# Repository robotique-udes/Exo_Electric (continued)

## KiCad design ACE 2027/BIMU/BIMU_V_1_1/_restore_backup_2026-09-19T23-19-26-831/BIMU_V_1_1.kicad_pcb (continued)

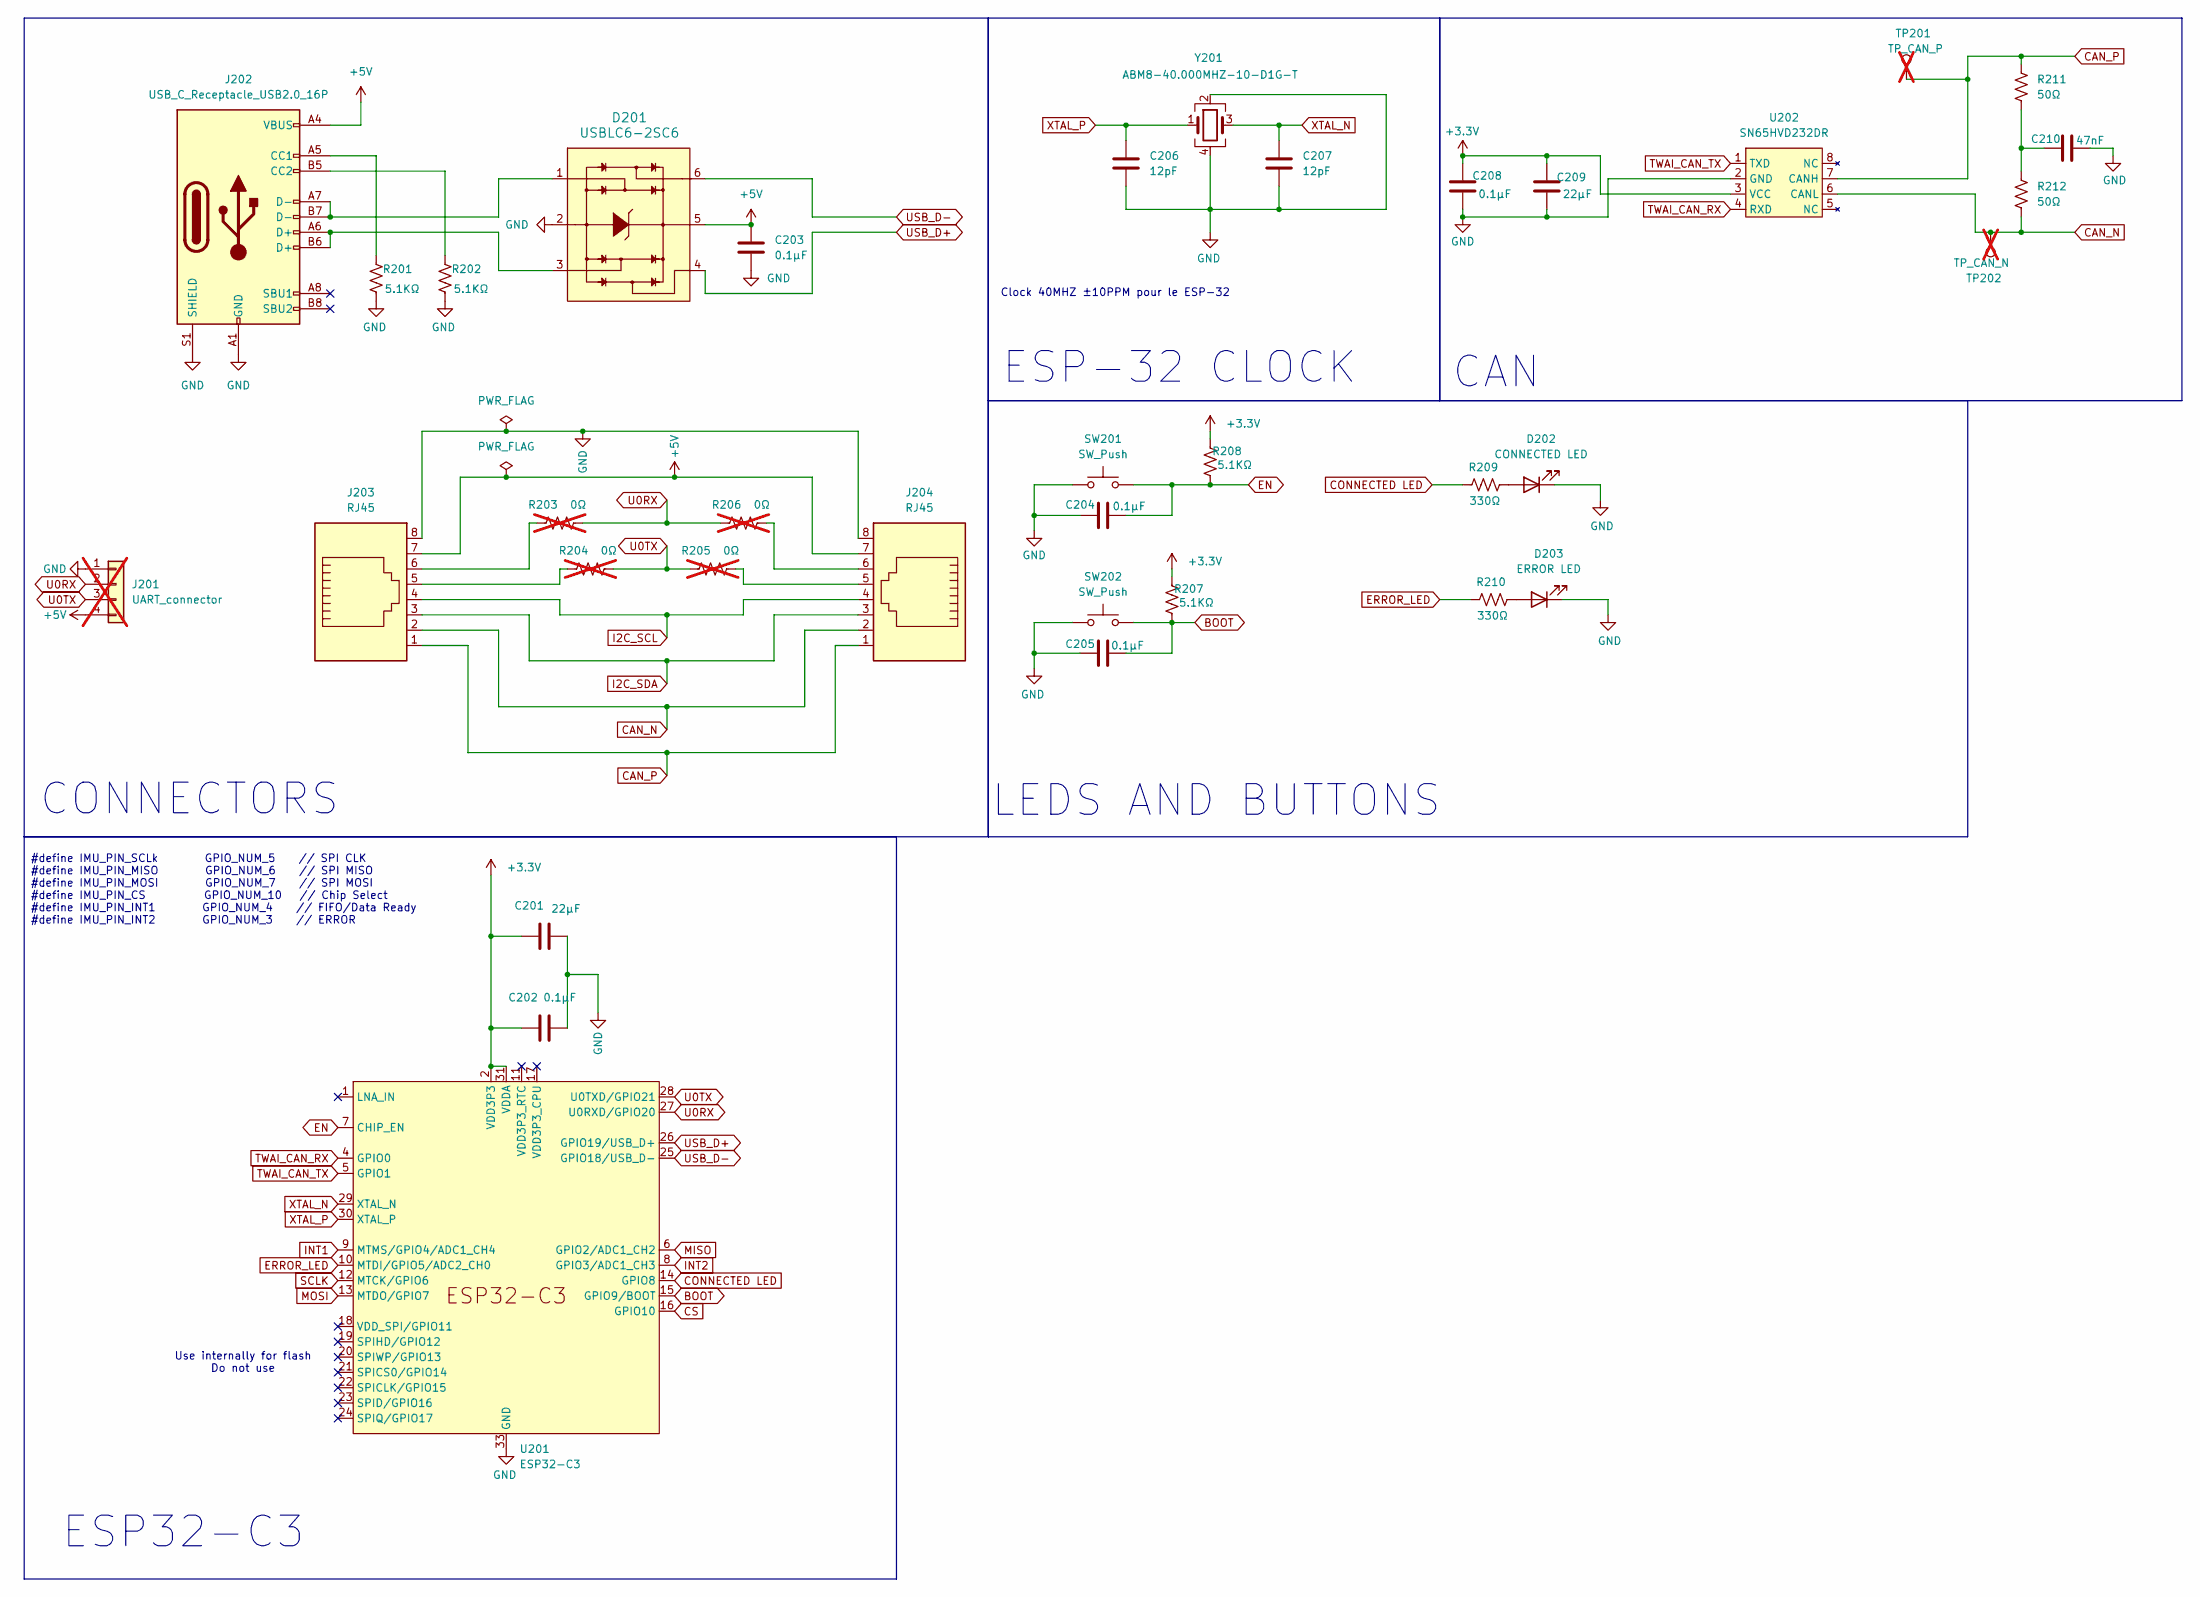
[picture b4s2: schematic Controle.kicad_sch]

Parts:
C201, C209: 22μF; C_0805_2012Metric_Pad1.18x1.45mm_HandSolder; Digi-Key_PN 1276-6501-1-ND
C202, C203, C204, C205, C208: 0.1μF; C_0805_2012Metric_Pad1.18x1.45mm_HandSolder; Digi-Key_PN 399-C0805C104K5RACTUCT-ND
C206, C207: 12pF; C_0805_2012Metric_Pad1.18x1.45mm_HandSolder; Digi-Key_PN 399-C0805C120J8HACTUCT-ND
C210: 47nF; C_0603_1608Metric_Pad1.08x0.95mm_HandSolder; Digi-Key_PN 1276-2960-1-ND
D201: USBLC6-2SC6; SOT23-6L; MPN USBLC6-2SC6; Digi-Key_PN 4518-USBLC6-2SC6CT-ND
D202: CONNECTED LED; LED_0805_2012Metric_Pad1.15x1.40mm_HandSolder; Digi-Key_PN 1516-QBLP631-IB5CT-ND
D203: ERROR LED; LED_0805_2012Metric_Pad1.15x1.40mm_HandSolder; Digi-Key_PN 1516-QBLP631-R5-2897CT-ND
J201: UART_connector; PinSocket_1x04_P2.54mm_Vertical; not fitted
J202: USB_C_Receptacle_USB2.0_16P; USB_C_Receptacle_GCT_USB4105-xx-A_16P_TopMnt_Horizontal; Digi-Key_PN 2073-USB4105-GF-ACT-ND
J203, J204: RJ45; RJ45_Amphenol_54602-x08_Horizontal; Digi-Key_PN 609-1046-ND
R201, R202, R207, R208: 5.1KΩ; R_0805_2012Metric_Pad1.20x1.40mm_HandSolder; Digi-Key_PN 541-CRCW08055K10FKEACCT-ND
R203, R204, R205, R206: 0Ω; R_0402_1005Metric_Pad0.72x0.64mm_HandSolder; not fitted
R209, R210: 330Ω; R_0805_2012Metric_Pad1.20x1.40mm_HandSolder; Digi-Key_PN 541-4168-1-ND
R211, R212: 50Ω; R_0805_2012Metric_Pad1.20x1.40mm_HandSolder; Digi-Key_PN 541-CRCW080550R0FKTACT-ND
SW201, SW202: SW_Push; SW_SPST_B3U-1000P; Digi-Key_PN SW1021CT-ND
TP201: TP_CAN_P; TestPoint_Pad_1.0x1.0mm; not fitted
TP202: TP_CAN_N; TestPoint_Pad_1.0x1.0mm; not fitted
U201: ESP32-C3; QFN-32-1EP_5x5mm_P0.5mm_EP3.45x3.45mm; Digi-Key_PN 1904-ESP32-C3FH4CT-ND
U202: SN65HVD232DR; SOIC-8_3.9x4.9mm_P1.27mm; Digi-Key_PN 296-26344-1-ND
Y201: ABM8-40.000MHZ-10-D1G-T; Crystal_SMD_2016-4Pin_2.0x1.6mm; Digi-Key_PN 535-14997-1-ND

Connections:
+3.3V: C201.1, C202.1, C208.1, C209.1, R207.2, R208.2, U201.2 (VDD3P3), U201.3 (VDD3P3), U201.31 (VDDA), U201.32 (VDDA), U202.3 (VCC); also elsewhere on the board
+5V: C203.1, D201.5, J201.4, J202.A4 (VBUS), J202.A9 (VBUS), J202.B4 (VBUS), J202.B9 (VBUS), J203.7, J204.7; also elsewhere on the board
BOOT: C205.1, R207.1, SW202.2, U201.15 (GPIO9/BOOT)
CAN_N: J203.2, J204.2, R212.2, TP202.1 (1_1), U202.6 (CANL); also elsewhere on the board
CAN_P: J203.1, J204.1, R211.1, TP201.1 (1_1), U202.7 (CANH); also elsewhere on the board
CONNECTED LED: R209.2, U201.14 (GPIO8)
CS: U201.16 (GPIO10); also elsewhere on the board
EN: C204.1, R208.1, SW201.2, U201.7 (CHIP_EN)
ERROR_LED: R210.2, U201.10 (MTDI/GPIO5/ADC2_CH0)
GND: C201.2, C202.2, C203.2, C204.2, C205.2, C206.2, C207.2, C208.2, C209.2, C210.1, D201.2, D202.1 (K), D203.1 (K), J201.1, J202.A1 (GND), J202.A12 (GND), J202.B1 (GND), J202.B12 (GND), J202.S1 (SHIELD), J203.8, J204.8, R201.2, R202.2, SW201.1, SW202.1, U201.33 (GND), U202.2 (GND), Y201.2, Y201.4; also elsewhere on the board
I2C_SCL: J203.4, J204.4
I2C_SDA: J203.3, J204.3
INT1: U201.9 (MTMS/GPIO4/ADC1_CH4); also elsewhere on the board
INT2: U201.8 (GPIO3/ADC1_CH3); also elsewhere on the board
MISO: U201.6 (GPIO2/ADC1_CH2); also elsewhere on the board
MOSI: U201.13 (MTDO/GPIO7); also elsewhere on the board
unnamed: C210.2, R211.2, R212.1
unnamed: D201.1, J202.A7 (D-), J202.B7 (D-)
unnamed: D201.3, J202.A6 (D+), J202.B6 (D+)
unnamed: D202.2 (A), R209.1
unnamed: D203.2 (A), R210.1
unnamed: J202.A5 (CC1), R201.1
unnamed: J202.B5 (CC2), R202.1
unnamed: J203.5, R204.1
unnamed: J203.6, R203.1
unnamed: J204.5, R205.2
unnamed: J204.6, R206.2
SCLK: U201.12 (MTCK/GPIO6); also elsewhere on the board
TWAI_CAN_RX: U201.4 (GPIO0), U202.4 (RXD)
TWAI_CAN_TX: U201.5 (GPIO1), U202.1 (TXD)
U0RX: J201.2, R203.2, R206.1, U201.27 (U0RXD/GPIO20)
U0TX: J201.3, R204.2, R205.1, U201.28 (U0TXD/GPIO21)
USB_D+: D201.4, U201.26 (GPIO19/USB_D+)
USB_D-: D201.6, U201.25 (GPIO18/USB_D-)
XTAL_N: C207.1, U201.29 (XTAL_N), Y201.3
XTAL_P: C206.1, U201.30 (XTAL_P), Y201.1

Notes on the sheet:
ESP32-C3
#define IMU_PIN_SCLk GPIO_NUM_5 // SPI CLK #define IMU_PIN_MISO GPIO_NUM_6 // SPI MISO #define IMU_PIN_MOSI GPIO_NUM_7 // SPI MOSI #define IMU_PIN_CS GPIO_NUM_10 // Chip Select #define IMU_PIN_INT1 GPIO_NUM_4 // FIFO/Data Ready #define IMU_PIN_INT2 GPIO_NUM_3 // ERROR
CONNECTORS
Use internally for flash Do not use
ESP-32 CLOCK
LEDS AND BUTTONS
CAN
Clock 40MHZ ±10PPM pour le ESP-32

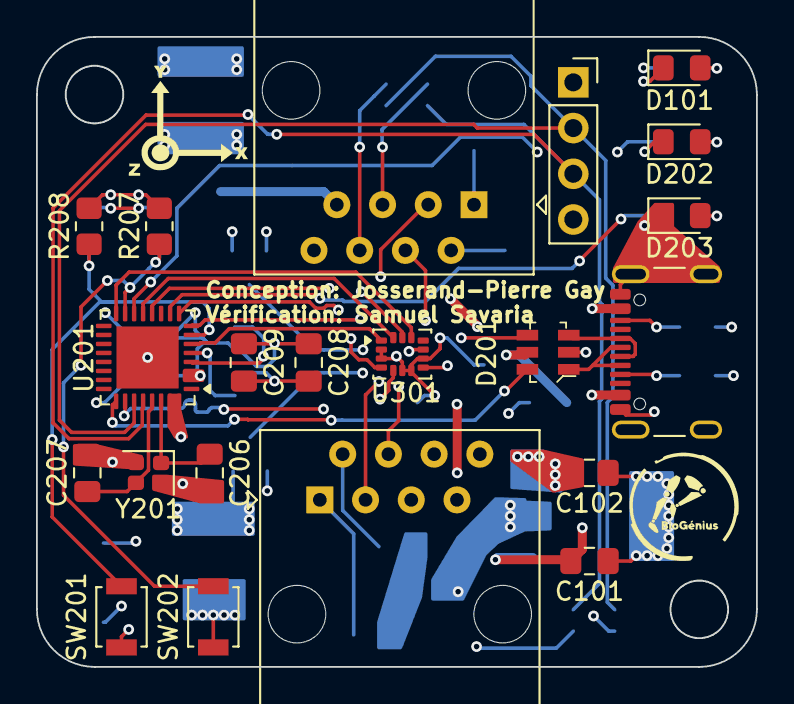
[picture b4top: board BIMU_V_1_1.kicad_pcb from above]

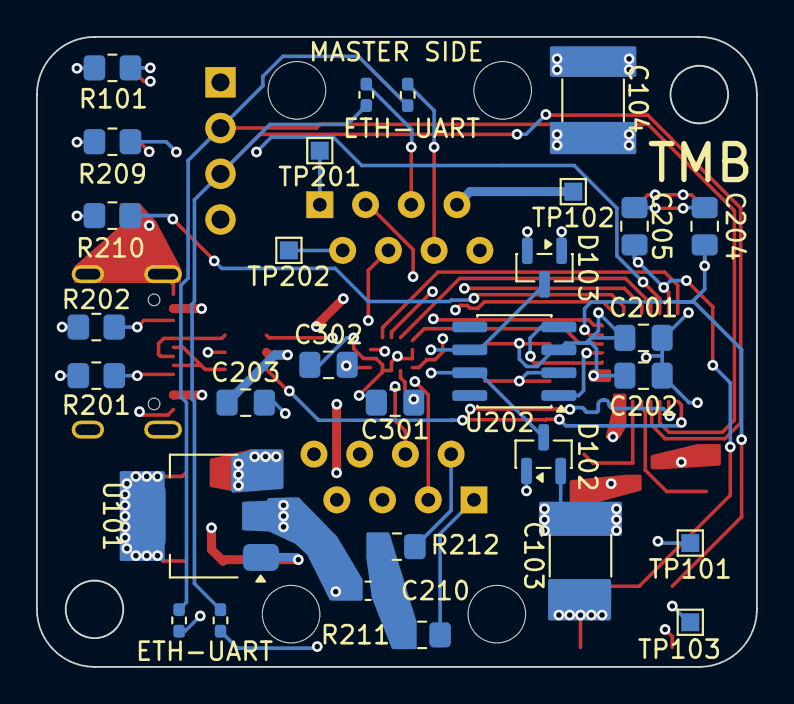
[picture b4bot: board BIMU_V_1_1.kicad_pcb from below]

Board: 4 copper layers, 40.0 x 35.0 mm, 53 parts (30 on the bottom side), 37 nets.

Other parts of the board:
C301, C302: 0.1μF; C_0805_2012Metric_Pad1.18x1.45mm_HandSolder
U301: LSM6DSV16BXTR; LGA-14_3x2.5mm_P0.5mm_LayoutBorder3x4y

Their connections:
+3.3V: C301.1, C302.2, U301.5 (VDDIO), U301.8 (VDD); also elsewhere on the board
CS: U301.12 (CS); also elsewhere on the board
GND: C301.2, C302.1, U301.2 (SDX), U301.3 (SCX), U301.6 (GND), U301.7 (GND), U301.9 (AH2); also elsewhere on the board
INT1: U301.4 (INT1); also elsewhere on the board
INT2: U301.10 (INT2); also elsewhere on the board
MISO: U301.1 (SDO/SA0); also elsewhere on the board
MOSI: U301.14 (SDA); also elsewhere on the board
SCLK: U301.13 (SCL); also elsewhere on the board

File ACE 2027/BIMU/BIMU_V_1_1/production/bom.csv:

Designator,Footprint,Quantity,Value,LCSC Part #
"C101, C102",0805,2,"4,7µF",
"C103, C104",1812,2,1nF,
"C201, C209",0805,2,22μF,
"C202, C203, C204, C205, C208, C301, C302",0805,7,0.1μF,
"C206, C207",0805,2,12pF,
C210,0603,1,47nF,
D101,0805,1,POWER LED,
"D102, D103",SOT-23,2,BAV99,
"D104, D105",0805,2,D_Schottky,
D201,SOT23-6L,1,USBLC6-2SC6,USBLC6-2SC6
D202,0805,1,CONNECTED LED,
D203,0805,1,ERROR LED,
J202,USB_C_Receptacle_GCT_USB4105-xx-A_16P_TopMnt_Horizontal,1,USB_C_Receptacle_USB2.0_16P,
"J203, J204",RJ45_Amphenol_54602-x08_Horizontal,2,RJ45,
"R101, R209, R210",0805,3,330Ω,
"R201, R202, R207, R208",0805,4,5.1KΩ,
"R203, R204, R205, R206",0402,4,0Ω,
"R211, R212",0805,2,50Ω,
"SW201, SW202",SW_SPST_B3U-1000P,2,SW_Push,
SW203,SW_SPDT_CK_JS102011SAQN,1,SW_CAN,
TP101,TestPoint_Pad_1.0x1.0mm,1,TP_GND_IN,
TP102,TestPoint_Pad_1.0x1.0mm,1,TP_5V,
TP103,TestPoint_Pad_1.0x1.0mm,1,TP_3v3,
TP201,TestPoint_Pad_1.0x1.0mm,1,TP_CAN_P,
TP202,TestPoint_Pad_1.0x1.0mm,1,TP_CAN_N,
U101,SOT-223-3_TabPin2,1,AP7361C-33E,
U201,QFN-32-1EP_5x5mm_P0.5mm_EP3.45x3.45mm,1,ESP32-C3,
U202,SOIC-8_3.9x4.9mm_P1.27mm,1,SN65HVD232DR,
U301,LGA-14_3x2.5mm_P0.5mm_LayoutBorder3x4y,1,LSM6DSV16BXTR,
Y201,Crystal_SMD_2016-4Pin_2.0x1.6mm,1,ABM8-40.000MHZ-10-D1G-T,

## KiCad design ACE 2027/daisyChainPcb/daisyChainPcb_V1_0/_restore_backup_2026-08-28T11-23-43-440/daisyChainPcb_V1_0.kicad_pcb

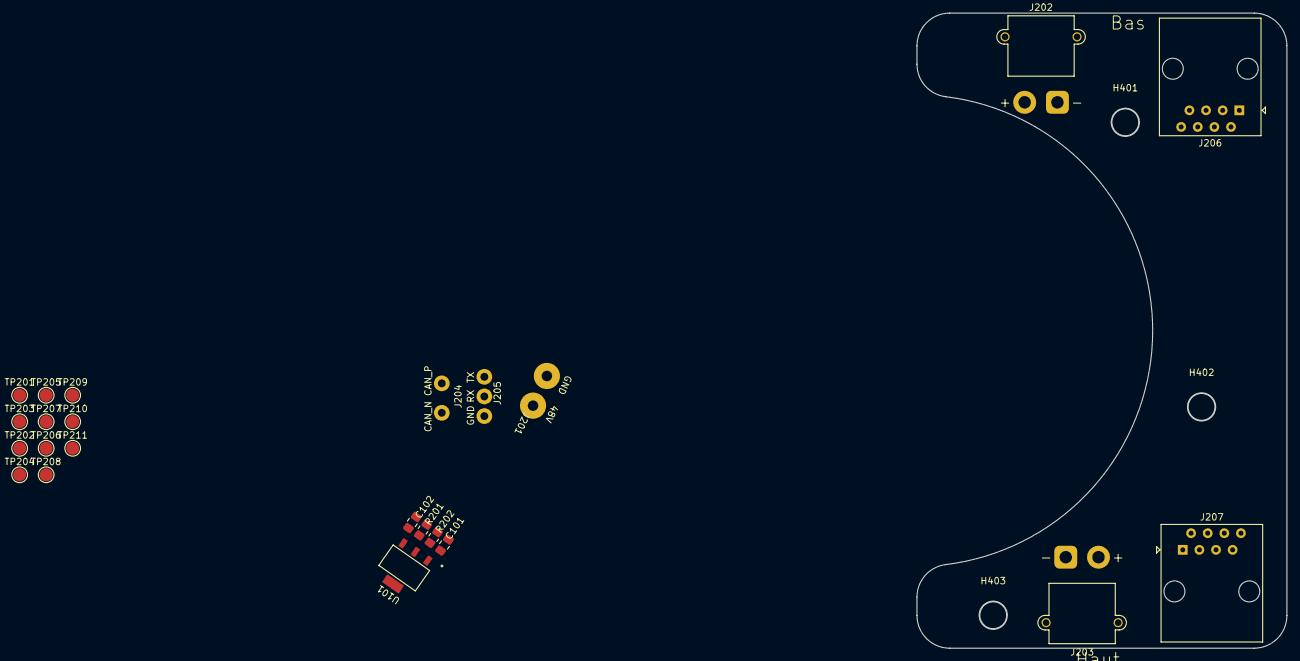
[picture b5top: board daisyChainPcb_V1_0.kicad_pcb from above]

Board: 2 copper layers, 56.5 x 97.0 mm, 26 parts (0 on the bottom side), 11 nets, no tracks yet.

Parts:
C101, C102: 4.7uF; C_0805_2012Metric_Pad1.18x1.45mm_HandSolder
H401, H402, H403: MountingHole; MountingHole_4.3mm_M4
J201: Pads; motorPads
J202, J203: XT30; AMASS_XT30PW-M_1x02_P2.50mm_Horizontal
J204: Pads; CAN_pads
J205: Pads; UART_pads
J206, J207: RJ45; RJ45_Amphenol_54602-x08_Horizontal
R201, R202: 1kΩ; R_0805_2012Metric_Pad1.20x1.40mm_HandSolder
TP201: CAN_P_TP; TestPoint_Pad_D2.0mm
TP202: SDA_TP; TestPoint_Pad_D2.0mm
TP203: CAN_N_TP; TestPoint_Pad_D2.0mm
TP204: SCL_TP; TestPoint_Pad_D2.0mm
TP205: TX_TP; TestPoint_Pad_D2.0mm
TP206: 5V_TP; TestPoint_Pad_D2.0mm
TP207: RX_TP; TestPoint_Pad_D2.0mm
TP208: GND_TP; TestPoint_Pad_D2.0mm
TP209: 48V_TP; TestPoint_Pad_D2.0mm
TP210: Power_GND_TP; TestPoint_Pad_D2.0mm
TP211: 3V3_TP; TestPoint_Pad_D2.0mm
U101: AP7361C-33E-13; SOT223_DIO-L

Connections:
+5V: C101.1, J206.7, J207.7, TP206.1 (1_1), U101.1 (IN)
/Controle/48V: J201.2, J202.2, J203.2
/Controle/CAN_N: J204.1, J206.2, J207.2, TP203.1 (1_1)
/Controle/CAN_P: J204.2, J206.1, J207.1, TP201.1 (1_1)
/Controle/RX: J205.2, J206.6, J207.6, TP207.1 (1_1)
/Controle/SCL: J206.4, J207.4, R201.1, TP204.1 (1_1)
/Controle/SDA: J206.3, J207.3, R202.1, TP202.1 (1_1)
/Controle/TX: J205.1, J206.5, J207.5, TP205.1 (1_1)
VCC_3V3: C102.1, R201.2, R202.2, TP211.1 (1_1), U101.3 (OUT)
power_GND: J201.1, J202.1, J203.1, TP210.1 (1_1)
signal_GND: C101.2, C102.2, J205.3, J206.8, J207.8, TP208.1 (1_1), U101.2 (GND), U101.4 (GND)

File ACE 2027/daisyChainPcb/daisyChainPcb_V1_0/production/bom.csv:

Designator,Footprint,Quantity,Value,LCSC Part #
"C101, C102",0805,2,4.7uF,
J201,motorPads,1,Pads,
"J202, J203",AMASS_XT30PW-M_1x02_P2.50mm_Horizontal,2,XT30,
J204,CAN_pads,1,Pads,
J205,UART_pads,1,Pads,
"J206, J207",RJ45_Amphenol_54602-x08_Horizontal,2,RJ45,
"R201, R202",0805,2,1kΩ,
TP201,TestPoint_Pad_D2.0mm,1,CAN_P_TP,
TP202,TestPoint_Pad_D2.0mm,1,SDA_TP,
TP203,TestPoint_Pad_D2.0mm,1,CAN_N_TP,
TP204,TestPoint_Pad_D2.0mm,1,SCL_TP,
TP205,TestPoint_Pad_D2.0mm,1,TX_TP,
TP206,TestPoint_Pad_D2.0mm,1,5V_TP,
TP207,TestPoint_Pad_D2.0mm,1,RX_TP,
TP208,TestPoint_Pad_D2.0mm,1,GND_TP,
TP209,TestPoint_Pad_D2.0mm,1,48V_TP,
TP210,TestPoint_Pad_D2.0mm,1,Power_GND_TP,
TP211,TestPoint_Pad_D2.0mm,1,3V3_TP,
U101,SOT223_DIO-L,1,AP7361C-33E-13,
